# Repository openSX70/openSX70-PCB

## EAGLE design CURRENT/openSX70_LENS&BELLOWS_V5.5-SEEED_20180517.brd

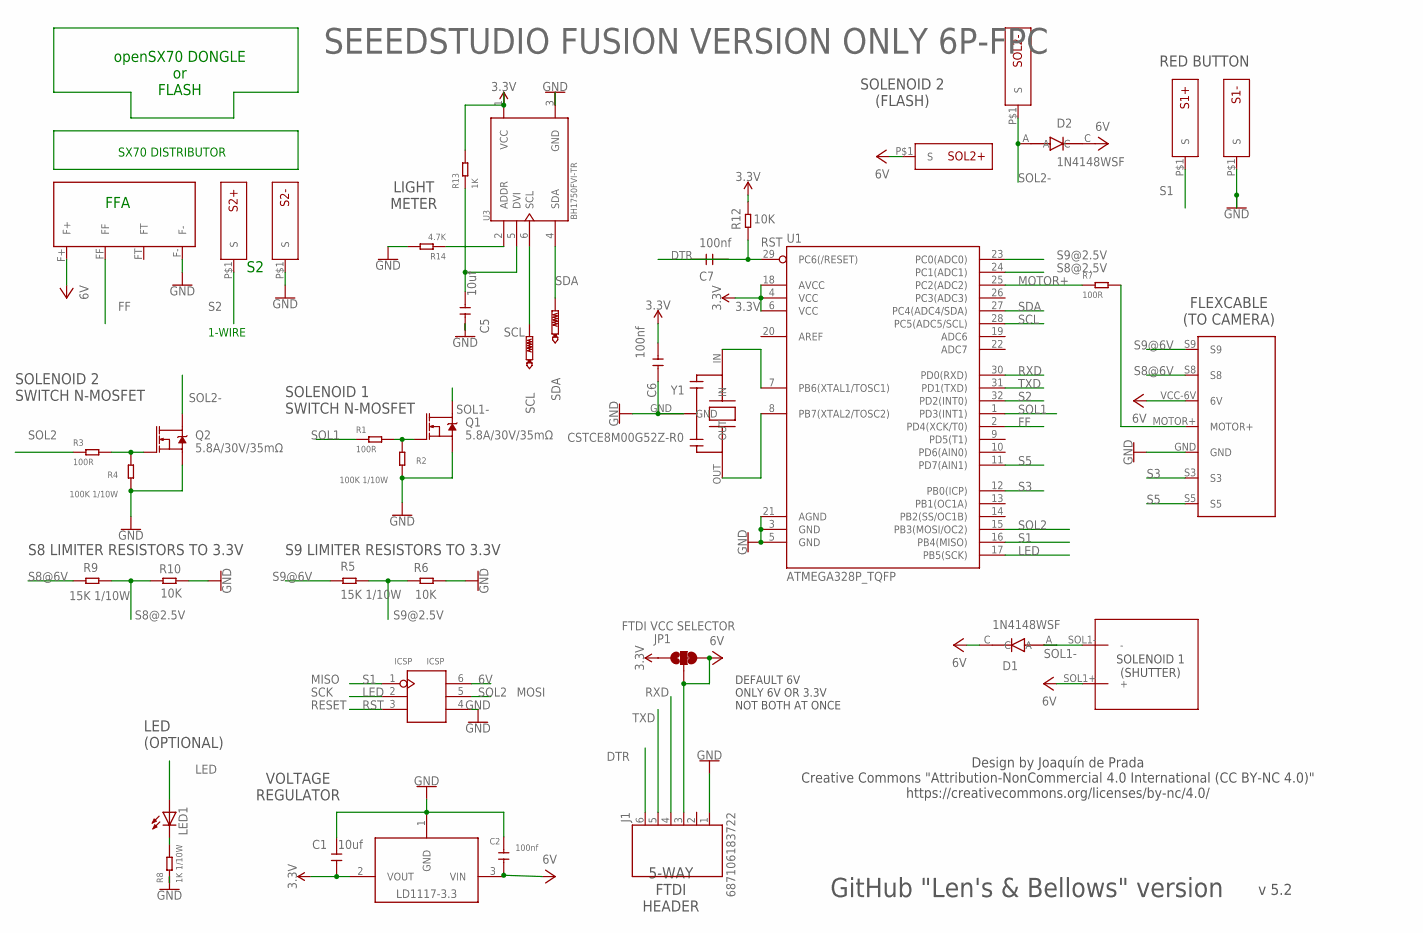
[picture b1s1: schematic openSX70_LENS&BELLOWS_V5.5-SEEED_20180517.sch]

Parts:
C1, C5: 10uf; C0603
C2, C6, C7: 100nf; C0603
D1, D2: 1N4148WSF; SODFL2512X100N
ICSP: ICSP; H2X3-2.54
J1: 687106183722
JP1: FTDI VCC SELECTOR; SMT-JUMPER_3_1-NC_TRACE_SILK
LD11172.5V: LD1117 2.5V; SOT223
LED1: LEDCHIPLED_0805; CHIPLED_0805
Q1, Q2: 5.8A/30V/35mΩ; SOT23-3
R1, R3, R7: 100R; R0603
R2, R4: 100K 1/10W; R0603
R5, R9: 15K 1/10W; R0603
R6, R10, R12: 10K; R0603
R8: 1K 1/10W; R0603
R13: 1K; R0603
R14: 4.7K; R0603
S1+, S1-, S2+, S2-: SX70-S-PAD-NEW; SX70-S-PAD2
SCL: PTR1TP08R; TP08R
SDA: PTR1TP08R; TP08R
SOL1: SX70-SOLENOID1-2PADS; SX70-SOLENOID1-2
SOL2+, SOL2-: SX70-S-PAD-NEW; SX70-S-PAD2
U1: ATMEGA328P_TQFP; TQFP32-08
U3: BH1750FVI-TR; SOTFL50P300X75-6N
U$1: SX70-7-PAD
U$2: FFA; FFA-PAD-PACKAGE
Y1: CSTCE8M00G52Z-R0; CFP95P160X100-3N

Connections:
3.3V: C1.2, C6.1, JP1.1, LD11172.5V.2 (VOUT), R12.2, R13.2, U1.4 (VCC), U1.6 (VCC), U1.18 (AVCC), U3.1 (VCC)
6V: C2.2, D1.C, D2.C, ICSP.6 (VCC), J1.3 (4), JP1.2, JP1.3, LD11172.5V.3 (VIN), SOL1.SOL1+ (+), SOL2+.P$1, U$1.VCC-6V (6V), U$2.F+
DTR: C7.1, J1.6 (1)
FF: U1.2 (PD4(XCK/T0)), U$2.FF
GND: C1.1, C2.1, C5.2, C6.2, ICSP.4 (GND), J1.1 (6), LD11172.5V.1 (GND), Q1.2 (S), Q2.2 (S), R2.1, R4.1, R6.2, R8.1, R10.2, R14.2, S1-.P$1, S2-.P$1, U1.3 (GND), U1.5 (GND), U1.21 (AGND), U3.3 (GND), U$1.GND, U$2.F-, Y1.GND
LED: ICSP.2 (SCK), LED1.A, U1.17 (PB5(SCK))
MOTOR+: R7.1, U1.25 (PC2(ADC2))
MOTOR-HEADER: R7.2, U$1.MOTOR+
unnamed: Q1.1 (G), R1.2, R2.2
unnamed: C5.1, R13.1, U3.5 (DVI)
unnamed: Q2.1 (G), R3.2, R4.2
unnamed: U1.7 (PB6(XTAL1/TOSC1)), Y1.IN
unnamed: LED1.C, R8.2
unnamed: U1.8 (PB7(XTAL2/TOSC2)), Y1.OUT
unnamed: R14.1, U3.2 (ADDR)
RST: C7.2, ICSP.3 (RST), R12.1, U1.29 (PC6(/RESET))
RXD: J1.4 (3), U1.30 (PD0(RXD))
S1: ICSP.1 (MISO), S1+.P$1, U1.16 (PB4(MISO))
S2: S2+.P$1, U1.32 (PD2(INT0))
S3: U1.12 (PB0(ICP)), U$1.S3
S5: U1.11 (PD7(AIN1)), U$1.S5
S8@2.5V: R9.2, R10.1, U1.24 (PC1(ADC1))
S8@6V: R9.1, U$1.S8
S9@2.5V: R5.2, R6.1, U1.23 (PC0(ADC0))
S9@6V: R5.1, U$1.S9
SCL: SCL.TP, U1.28 (PC5(ADC5/SCL)), U3.6 (SCL)
SDA: SDA.TP, U1.27 (PC4(ADC4/SDA)), U3.4 (SDA)
SOL1: R1.1, U1.1 (PD3(INT1))
SOL1-: D1.A, Q1.3 (D), SOL1.SOL1- (-)
SOL2: ICSP.5 (MOSI), R3.1, U1.15 (PB3(MOSI/OC2))
SOL2-: D2.A, Q2.3 (D), SOL2-.P$1
TXD: J1.5 (2), U1.31 (PD1(TXD))

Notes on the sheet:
1-WIRE
FFA
LIGHT METER
FLEXCABLE (TO CAMERA)
RED BUTTON
SOLENOID 1 (SHUTTER)
SOLENOID 2 (FLASH)
5-WAY FTDI HEADER
VOLTAGE REGULATOR
LED (OPTIONAL)
S8 LIMITER RESISTORS TO 3.3V
S9 LIMITER RESISTORS TO 3.3V
SOLENOID 2 SWITCH N-MOSFET
SOLENOID 1 SWITCH N-MOSFET
SX70 DISTRIBUTOR
openSX70 DONGLE or FLASH
v 5.2
Design by Joaquín de Prada Creative Commons "Attribution-NonCommercial 4.0 International (CC BY-NC 4.0)" https://creativecommons.org/licenses/by-nc/4.0/
GitHub "Len's & Bellows" version
DEFAULT 6V ONLY 6V OR 3.3V NOT BOTH AT ONCE
SEEEDSTUDIO FUSION VERSION ONLY 6P-FPC
MISO
SCK
RESET
MOSI

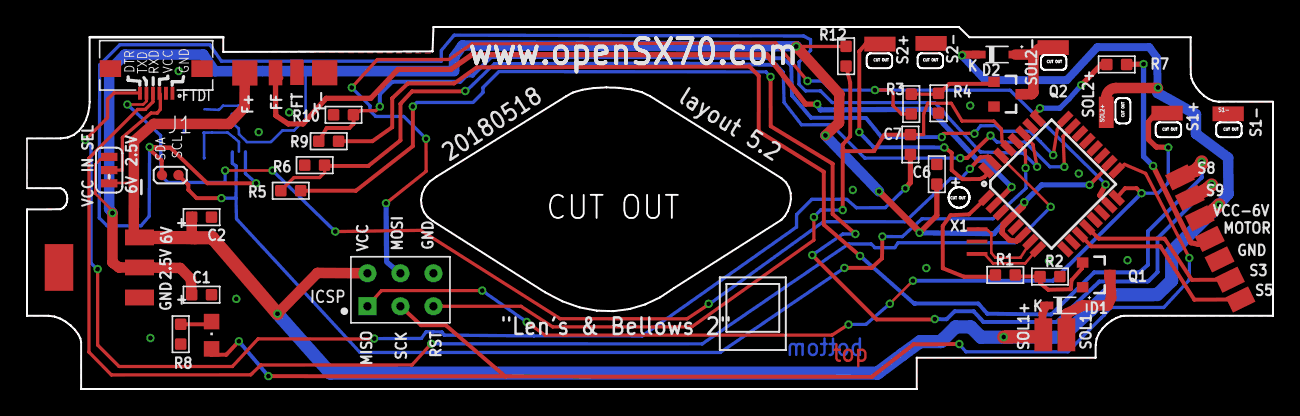
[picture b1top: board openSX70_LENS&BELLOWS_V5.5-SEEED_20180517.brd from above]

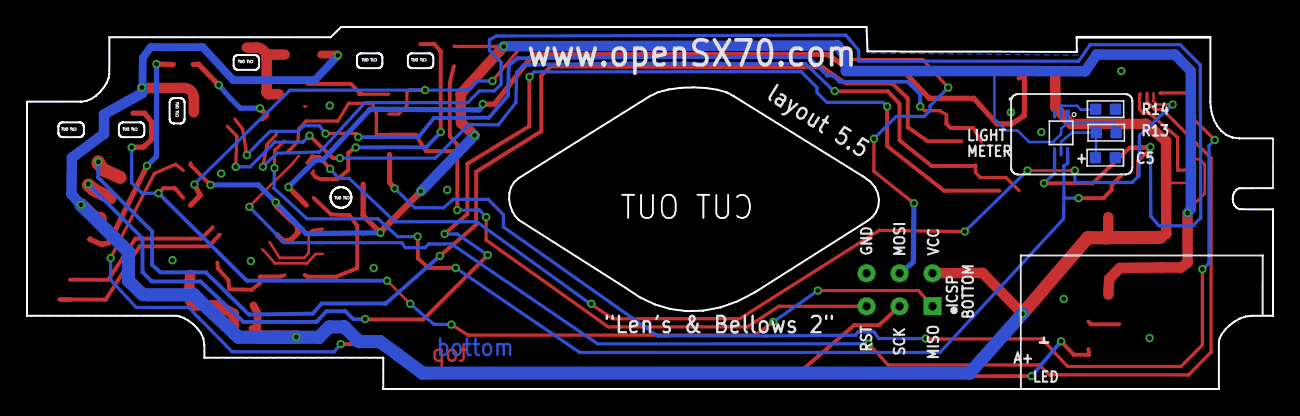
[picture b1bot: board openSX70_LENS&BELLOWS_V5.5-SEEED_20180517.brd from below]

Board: 2 copper layers, 95.9 x 27.9 mm, 41 parts (4 on the bottom side), 32 nets.

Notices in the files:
parts and their libraries:
SparkFun-Jumpers: Licensing: Creative Commons ShareAlike 4.0 International - https://creativecommons.org/licenses/by-sa/4.0
